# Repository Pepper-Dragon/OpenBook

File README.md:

# OpenBook
Proiect TSC - Diaconu Andrei 331CB

## Block Diagram

## Components

- **Microcontroller:** ESP32-C6 with integrated Wi-Fi 6 and Bluetooth 5 — responsible for core processing, communication, and power management.
- **Display:** 800×480 resolution e-Paper (e-Ink) display interfaced via SPI — ideal for low-power, high-visibility content rendering.
- **Sensors:** BME688 environmental sensor (temperature, humidity, pressure, air quality) connected through I2C.
- **Power Supply:** 2500mAh LiPo battery with USB-C charging and integrated fuel gauge for real-time battery monitoring.
- **Storage:** MicroSD card slot for storing e-books and other resources, communicating via SPI.
- **Real-Time Clock:** DS3231 RTC module with battery backup for accurate timekeeping even during power loss.
- **User Inputs:** 3 buttons (connected via GPIO) for navigation and control.
- **Expansion Options:** QWIIC/Stemma QT connector for easy integration of additional sensors or modules.

## Bill Of Materials

|                                   name                                   	|        value       	| description                                                           	| quantity 	|                                                                                                                                                     link                                                                                                                                                    	| datasheet                                                                                                                           	|
|:------------------------------------------------------------------------:	|:------------------:	|-----------------------------------------------------------------------	|:--------:	|:-----------------------------------------------------------------------------------------------------------------------------------------------------------------------------------------------------------------------------------------------------------------------------------------------------------:	|-------------------------------------------------------------------------------------------------------------------------------------	|
| LED1                                                                     	|          -         	| LED                                                                   	| 1        	| [link](https://www.niden.ro/led-uri-smd/4560-led-smd-0603-alb-rece.html)                                                                                                                                                                                                                                    	| [link](https://www.mouser.com/datasheet/2/423/LSM0603472V_(1)-1379786.pdf?srsltid=AfmBOoqdcB2pVIrWRImdZdFZcxn5SIjNLKeNM1u-ULY7G7UgiZHJYMAt)	|
| C18                                                                      	|      0.1uF/50V     	| CAPACITOR, European symbol                                            	| 1        	| [link](https://ro.mouser.com/ProductDetail/KEMET/C0402C104K4RAC7411?qs=GedzDrHbfJPMv36lRRfk4g%3D%3D)                                                                                                                                                                                                                	| [link](https://ro.mouser.com/datasheet/2/447/KEM_C1002_X7R_SMD-3316098.pdf)                                                                 	|
| R5                                                                       	|        0.47        	| RESISTOR, European symbol                                             	| 1        	| [link](https://ro.mouser.com/ProductDetail/ROHM-Semiconductor/SFR01MZPJ471?qs=sGAEpiMZZMtlubZbdhIBIONtIqra%2FA5YbUieG7R0owU%3D)                                                                                                                                                                                     	| [link](https://fscdn.rohm.com/en/products/databook/datasheet/passive/resistor/chip_resistor/sfr-e.pdf)                                      	|
| R1                                                                       	|        100K        	| RESISTOR, European symbol                                             	| 1        	| [link](https://ro.mouser.com/ProductDetail/Bourns/CR0402-FX-1003GLF?qs=URDPQ%2Fj0cz1ZruPSJQ7fsA%3D%3D&utm_id=6470900573&utm_source=google&utm_medium=cpc&utm_marketing_tactic=emeacorp&gad_source=1&gclid=CjwKCAjwzMi_BhACEiwAX4YZUExf8o5xv9o__WAln9moW8yaWJv0M179-dCfAxoyQP6_ulvhYGGM9xoCahIQAvD_BwE)              	| [link](https://ro.mouser.com/datasheet/2/54/cr-1858361.pdf)                                                                                 	|
| C1, C5, C21, C22, C23, C25, C26, C27                                     	|        100nF       	| CAPACITOR, European symbol                                            	| 8        	| [link](https://ro.mouser.com/ProductDetail/KEMET/C0402C104K4RAC7411?qs=GedzDrHbfJPMv36lRRfk4g%3D%3D)                                                                                                                                                                                                                	| [link](https://ro.mouser.com/datasheet/2/447/KEM_C1002_X7R_SMD-3316098.pdf)                                                                 	|
| C2                                                                       	|        100uF       	| POLARIZED CAPACITOR, European symbol                                  	| 1        	| [link](https://ro.mouser.com/ProductDetail/KEMET/T491B107M006AT?qs=U312oeP%2FpiHOgyk6KO2m0g%3D%3D)                                                                                                                                                                                                                  	| [link](https://ro.mouser.com/datasheet/2/447/KEM_T2005_T491-3316937.pdf)                                                                    	|
| R18                                                                      	|         10K        	| RESISTOR, European symbol                                             	| 1        	| [link](https://ro.mouser.com/ProductDetail/Vishay-Dale/CRCW040210K0FKEDC?qs=E3Y5ESvWgWPiNLcGzwCGPg%3D%3D)                                                                                                                                                                                                           	| [link](https://www.vishay.com/docs/28773/crcwce3.pdf)                                                                                       	|
| R6, R10, R11, R12, R13, R14, R15, R16, R19, R20, R21, R22, R23, R24, R25 	|         10k        	| RESISTOR, European symbol                                             	| 15       	| [link](https://ro.mouser.com/ProductDetail/Vishay-Dale/CRCW040210K0FKEDC?qs=E3Y5ESvWgWPiNLcGzwCGPg%3D%3D)                                                                                                                                                                                                           	| [link](https://www.vishay.com/docs/28773/crcwce3.pdf)                                                                                       	|
| C7                                                                       	|        10uF        	| CAPACITOR, European symbol                                            	| 1        	| [link](https://ro.mouser.com/ProductDetail/KEMET/C0402C106M7PAC7867?qs=kZJHmUDErizJnkDIcqVWRQ%3D%3D)                                                                                                                                                                                                                	| [link](https://ro.mouser.com/datasheet/2/447/KEM_C1006_X5R_SMD-3316465.pdf)                                                                 	|
| J1                                                                       	|          -         	| Micro SD Card Socket, Push-Push Type, Top   Mount, SMT, H=1.83mm, 10u 	| 1        	| [link](https://www.digikey.ro/en/products/detail/attend-technology/112A-TAAR-R03/17633923)                                                                                                                                                                                                                          	| [link](https://www.attend.com.tw/data/download/file/112A-TAAR-R03_Spec.pdf)                                                                 	|
| R17                                                                      	|         15         	| RESISTOR, European symbol                                             	| 1        	| [link](https://www.soselectronic.com/ro-ro/products/yageo/r0402-5-15-r-rc0402jr-0715rl-1-81614)                                                                                                                                                                                                                     	| [link](https://cdn.soselectronic.com/productdata/4b/af/65353ac1/r0402-1-1-5-k-rc0402fr-071k5l-1.pdf)                                        	|
| C24                                                                      	|         1uF        	| CAPACITOR, European symbol                                            	| 1        	| [link](https://ro.mouser.com/ProductDetail/KEMET/C0402C105Z9VACTU?qs=gt1LBUVyoHlQieoJt4iw1w%3D%3D)                                                                                                                                                                                                                  	| [link](https://ro.mouser.com/datasheet/2/447/KEM_C1005_Y5V_SMD-3316374.pdf)                                                                 	|
| C11, C12, C13, C14, C15, C16, C17, C19, C20                              	|       1uF/50V      	| CAPACITOR, European symbol                                            	| 9        	| [link](https://ro.mouser.com/ProductDetail/KEMET/C0402C105Z9VACTU?qs=gt1LBUVyoHlQieoJt4iw1w%3D%3D)                                                                                                                                                                                                                  	| [link](https://ro.mouser.com/datasheet/2/447/KEM_C1005_Y5V_SMD-3316374.pdf)                                                                 	|
| R7                                                                       	|         2.2        	| RESISTOR, European symbol                                             	| 1        	| [link](https://ro.mouser.com/ProductDetail/Panasonic/ERJ-PA2J2R2X?qs=sGAEpiMZZMtlubZbdhIBIKn8wLs5z3UnO%252BN6Zqj8Y2A%3D)                                                                                                                                                                                            	| [link](https://industrial.panasonic.com/cdbs/www-data/pdf/RDO0000/AOA0000C331.pdf)                                                          	|
| R8                                                                       	|         200        	| RESISTOR, European symbol                                             	| 1        	| [link](https://ro.mouser.com/ProductDetail/Vishay-Thin-Film/PNM0402E2000BSTS?qs=sGAEpiMZZMvdGkrng054t2cqbZCzJY7NtycrwNLdAiqcSryq%252B1Rhtw%3D%3D)                                                                                                                                                                   	| [link](https://www.vishay.com/docs/60057/pnm.pdf)                                                                                           	|
| Q1, Q3                                                                   	| 20V/4.2A/52mO/1.4W 	| P-channel MOSFETs                                                     	| 2        	| [link](https://www.digikey.ro/en/products/detail/vishay-siliconix/SI1308EDL-T1-GE3/4876435?utm_campaign=buynow&utm_medium=aggregator&utm_source=snapeda)                                                                                                                                                            	| [link](https://www.vishay.com/docs/63399/si1308edl.pdf)                                                                                     	|
| R9                                                                       	|         2k         	| RESISTOR, European symbol                                             	| 1        	| [link](https://ro.mouser.com/ProductDetail/Vishay-Dale/CRCW04022K00FKEE?qs=raETa%252B32nO8lGcRW9MjUBA%3D%3D)                                                                                                                                                                                                        	| [link](https://www.vishay.com/docs/20035/dcrcwe3.pdf)                                                                                       	|
| C6, C9, C10                                                              	|        4.7uF       	| CAPACITOR, European symbol                                            	| 3        	| [link](https://ro.mouser.com/ProductDetail/KEMET/C0402C475K8PACTU?qs=ulEaXIWI0c9ebKRT3r3htg%3D%3D)                                                                                                                                                                                                                  	| [link](https://ro.mouser.com/datasheet/2/447/KEM_C1006_X5R_SMD-3316465.pdf)                                                                 	|
| C3, C4                                                                   	|        4.7uF       	| CAPACITOR, European symbol                                            	| 2        	| [link](https://ro.mouser.com/ProductDetail/KEMET/C0402C475K8PACTU?qs=ulEaXIWI0c9ebKRT3r3htg%3D%3D)                                                                                                                                                                                                                  	| [link](https://ro.mouser.com/datasheet/2/447/KEM_C1006_X5R_SMD-3316465.pdf)                                                                 	|
| C8                                                                       	|      4.7uF/25V     	| CAPACITOR, European symbol                                            	| 1        	| [link](https://ro.mouser.com/ProductDetail/KEMET/C0402C475K8PACTU?qs=ulEaXIWI0c9ebKRT3r3htg%3D%3D)                                                                                                                                                                                                                  	| [link](https://ro.mouser.com/ProductDetail/KEMET/C0402C475K8PACTU?qs=ulEaXIWI0c9ebKRT3r3htg%3D%3D)                                          	|
| D3                                                                       	|      4.7uF/25V     	| ON SEMICONDUCTOR - MBR0530 - DIODE,   SCHOTTKY, 0.5A, 30V, SOD-123    	| 1        	| [link](https://www.snapeda.com/parts/MBR0530/Onsemi/view-part/?ref=eda)                                                                                                                                                                                                                                             	| [link](https://www.snapeda.com/parts/MBR0530/ON%20Semiconductor/datasheet/)                                                                 	|
| R3, R4                                                                   	|         5k1        	| RESISTOR, European symbol                                             	| 2        	| [link](https://www.gme.cz/v/1484336/yageo-r0402-5k1-006w-1-smd-rezistor?srsltid=AfmBOooJFe0JuMtJCHsiAAMzt535X2PaRQWliIdlncts6E1iAX--2xYh)                                                                                                                                                                           	| [link](https://img.gme.cz/files/eshop_data/eshop_data/7/984-017/dsh.984-017.1.pdf)                                                          	|
| L1                                                                       	|        68uH        	| coil                                                                  	| 1        	| [link](https://ro.mouser.com/ProductDetail/Wurth-Elektronik/744043680?qs=PGXP4M47uW6VkZq%252BkzjrHA%3D%3D)                                                                                                                                                                                                          	| [link](https://www.we-online.com/components/products/datasheet/744043680.pdf)                                                               	|
| IC2                                                                      	|          -         	| Voltage Detector with Adjustable Delay                                	| 1        	| [link](https://ro.mouser.com/ProductDetail/ROHM-Semiconductor/BD5229G-TR?qs=4kLU8WoGk0vvnhrrYwdszw%3D%3D)                                                                                                                                                                                                           	| [link](https://fscdn.rohm.com/en/products/databook/datasheet/ic/power/voltage_detector/bd52xxg-e.pdf)                                       	|
| BOOT_BUTTON, CHANGE_BUTTON, RESET_BUTTON                                 	|          -         	| Button                                                                	| 3        	| [link](https://ro.mouser.com/ProductDetail/CK/PTS841-GK-SMTR-LFS?qs=d0WKAl%252BL4KbAtAqJT9yhkg%3D%3D)                                                                                                                                                                                                               	| [link](https://www.ckswitches.com/media/2805/pts841.pdf)                                                                                    	|
| C28                                                                      	|          -         	| Cap 0.011F 3.3V 1210 Flat                                             	| 1        	| [link](https://www.snapeda.com/parts/CPH3225A/Seiko+Instruments/view-part/?ref=eda)                                                                                                                                                                                                                                 	| [link](https://www.snapeda.com/parts/CPH3225A/Seiko%20Instruments/datasheet/)                                                               	|
| U5                                                                       	|          -         	| Real Time Clock Serial 16-Pin SOIC W   T/R                            	| 1        	| [link](https://www.snapeda.com/parts/DS3231SN%23/Analog+Devices/view-part/?ref=eda)                                                                                                                                                                                                                                 	| [link](https://www.snapeda.com/parts/DS3231SN%23/Analog%20Devices/datasheet/)                                                               	|
| U2                                                                       	|          -         	| ESP32                                                                 	| 1        	| [link](https://www.snapeda.com/parts/ESP32-C6-WROOM-1-N8/Espressif+Systems/view-part/?ref=eda)                                                                                                                                                                                                                      	| [link](https://www.snapeda.com/parts/ESP32-C6-WROOM-1-N8/Espressif%20Systems/datasheet/)                                                    	|
| R2                                                                       	|          -         	| VARISTOR                                                              	| 1        	| [link](https://www.digikey.ro/en/products/detail/epcos-tdk-electronics/B72580T0110K062/15903564)                                                                                                                                                                                                                    	| [link](https://www.tdk-electronics.tdk.com/inf/75/db/CTVS_14/Standard_series.pdf)                                                           	|
| D1, D6                                                                   	|          -         	| Schottky Barrier Rectifier Diode                                      	| 2        	| [link](https://eu.mouser.com/ProductDetail/KYOCERA-AVX/SD0805S020S1R0?qs=jCA%252BPfw4LHbpkAoSnwrdjw%3D%3D&srsltid=AfmBOoos7vAXHpuNsFyDZDH2ms56jfFYgACPLwGeQRLBDVu-QQCPVRyy)                                                                                                                                         	| [link](https://ro.mouser.com/datasheet/2/40/schottky-3165252.pdf)                                                                           	|
| U3                                                                       	|          -         	| Integrated Environmental Unit                                         	| 1        	| [link](https://ro.mouser.com/ProductDetail/Bosch-Sensortec/BME680?qs=v271MhAjFHjo0yA%2FC4OnDQ%3D%3D)                                                                                                                                                                                                                	| [link](https://ro.mouser.com/datasheet/2/783/BST_BME680_DS001-1509608.pdf)                                                                  	|
| U1                                                                       	|          -         	| MCP73831T Li-Ion, Li-Pol Controller                                   	| 1        	| [link](https://eu.mouser.com/ProductDetail/Microchip-Technology/MCP73831T-2ACI-OT?qs=yUQqVecv4qvbBQBGbHx0Mw%3D%3D&utm_id=20109199409&utm_source=google&utm_medium=cpc&utm_marketing_tactic=emeacorp&gad_source=1&gclid=CjwKCAjwzMi_BhACEiwAX4YZUFXFfoOvOVw-rJ3AqbhBnSMrJwio_-4FjBZgwNJVbUQHlwwnAKDqhBoCYr4QAvD_BwE) 	| [link](https://ro.mouser.com/datasheet/2/268/MCP73831_Family_Data_Sheet_DS20001984H-3441711.pdf)                                            	|
| J3                                                                       	|          -         	|  (0.50mm) Surface Mount, Right Angle                                  	| 1        	| [link](https://ro.mouser.com/ProductDetail/Hirose-Connector/FH34SRJ-24S-0.5SH99?qs=vcbW%252B4%252BSTIpKBl5ap9J8Fw%3D%3D&_gl=1*l9suft*_ga*MTI5Mzc0MzA3OS4xNzQzODQ5MDQz*_ga_15W4STQT4T*MTc0Mzk1NTYyNy40LjAuMTc0Mzk1NTYyNy42MC4wLjA.)                                                                                  	| [link](https://ro.mouser.com/datasheet/2/185/FH34SRJ_24S_0_5SH_99__CL0580_1255_6_99_2DDrawing_0-1615044.pdf)                                	|
| U4                                                                       	|          -         	| 3µA 1-Cell/2-Cell Fuel Gauge with ModelGauge                          	| 1        	| [link](https://www.snapeda.com/parts/MAX17048G+T10/Analog+Devices/view-part/?ref=eda)                                                                                                                                                                                                                               	| [link](https://www.snapeda.com/parts/MAX17048G+T10/Analog%20Devices/datasheet/)                                                             	|
| D4, D5                                                                   	|          -         	| DIODE,   SCHOTTKY, 0.5A, 30V, SOD-123                                 	| 2        	| [link](https://www.snapeda.com/parts/MBR0530/Onsemi/view-part/?ref=eda)                                                                                                                                                                                                                                             	| [link](https://www.snapeda.com/parts/MBR0530/ON%20Semiconductor/datasheet/)                                                                 	|
| D7, D8, D9, D10, D11, D12                                                	|          -         	| Ipp Tvs Diode                                                         	| 6        	| [link](https://www.snapeda.com/parts/PGB1010603MR/Littelfuse/view-part/?ref=eda)                                                                                                                                                                                                                                    	| [link](https://www.snapeda.com/parts/PGB1010603MR/Littelfuse%20Inc./datasheet/)                                                             	|
| J4                                                                       	|          -         	| SparkFun I2C Standard Qwiic Connector                                 	| 1        	| [link](https://www.sparkfun.com/qwiic-jst-connector-smd-4-pin-horizontal.html)                                                                                                                                                                                                                                      	| [link](https://cdn.sparkfun.com/assets/parts/1/2/2/8/9/Qwiic_Connector_Datasheet.pdf)                                                       	|
| J2                                                                       	|          -         	| CONN USB 2.0 TYPE-C R/A SMT                                           	| 1        	| [link](https://ro.mouser.com/ProductDetail/GCT/USB4110-GF-A?qs=KUoIvG%2F9IlYiZvIXQjyJeA%3D%3D)                                                                                                                                                                                                                      	| [link](https://ro.mouser.com/datasheet/2/837/GCT_USB4110_Product_Drawing___20k_cycles-3455479.pdf)                                          	|
| Q2                                                                       	|          -         	| MOSFET N-Ch 30V 1.5A                                                  	| 1        	| [link](https://www.snapeda.com/parts/SI1308EDL-T1-GE3/Vishay+Siliconix/view-part/?ref=eda)                                                                                                                                                                                                                          	| [link](https://www.snapeda.com/parts/SI1308EDL-T1-GE3/Vishay%20Siliconix/datasheet/)                                                        	|
| D2                                                                       	|          -         	| Low Cap. ESD Protection Auto SOT-23-6                                 	| 1        	| [link](https://www.snapeda.com/parts/USBLC6-2SC6Y/STMicroelectronics/view-part/?ref=eda)                                                                                                                                                                                                                            	| [link](https://www.snapeda.com/parts/USBLC6-2SC6Y/STMicroelectronics/datasheet/)                                                            	|
| U6                                                                       	|          -         	| FLASH - NOR Memory IC 512Mb                                           	| 1        	| [link](https://www.snapeda.com/parts/W25Q512JVEIQ/Winbond+Electronics/view-part/?ref=eda)                                                                                                                                                                                                                           	| [link](https://www.snapeda.com/parts/W25Q512JVEIQ/Winbond%20Electronics/datasheet/)                                                         	|
| IC1                                                                      	|          -         	| LDO Voltage Regulator                                                 	| 1        	| [link](https://ro.mouser.com/ProductDetail/Torex-Semiconductor/XC6220A331MR-G?qs=AsjdqWjXhJ8ZSWznL1J0gg%3D%3D&utm_id=6470900573&utm_source=google&utm_medium=cpc&utm_marketing_tactic=emeacorp&gad_source=1&gclid=CjwKCAjwzMi_BhACEiwAX4YZUHiB3kDs66vv29tGnRc8y1huoaOvdBlKkwXVy8QKs7T5wBQH4NGZUxoCU5wQAvD_BwE)      	| [link](https://ro.mouser.com/datasheet/2/760/xc6220-3371556.pdf)                                                                            	|

## ESP32-C6 Pins

| Connection      | Pin            | Description                                                               |
|-----------------|----------------|---------------------------------------------------------------------------|
| **RESET**       | EN             | Reset button for initiating a reset sequence                              |
| **INT_RTC**     | IO0            | Interrupt signal for the RTC                                              |
| **32KHZ**       | IO1            | Input for 32kHz clock signal                                              |
| **MISO**        | IO2            | Master In Slave Out for communication between the microcontroller, Flash, SD Card, and display |
| **EPD_BUSY**    | IO3            | Signal indicating if the display is busy                                  |
| **SS_SD**       | IO4            | Chip select for the SD card                                               |
| **EPD_DC**      | IO5            | Display data/command control pin                                          |
| **SCK**         | IO6            | SPI clock for synchronizing data transfers                                |
| **MOSI**        | IO7            | Master Out Slave In for data transmission between the microcontroller, Flash, SD card, and display |
| **3V3**         | IO8            | 3.3V power supply                                                          |
| **IO/BOOT**     | IO9            | Boot button to trigger boot process                                       |
| **EPD_CS**      | IO10           | Chip select for the display                                               |
| **FLASH_CS**    | IO11           | Chip select for the Flash memory                                          |
| **USB_D-**      | IO12           | USB data negative for communication                                       |
| **USB_D+**      | IO13           | USB data positive for communication                                       |
| **IO/CHANGE**   | IO15           | Button to trigger a change action                                         |
| **TX (UART)**   | TXD0 / GPIO16  | Serial transmitter for UART communication                                 |
| **RX (UART)**   | RXD0 / GPIO17  | Serial receiver for UART communication                                    |
| **RTC_RST**     | IO18           | External reset for the RTC module                                         |
| **I2C_PW**      | IO19           | Power control signal for I2C devices                                      |
| **EPD_3V3_C**   | IO20           | 3.3V power supply for the display                                         |
| **SDA (I2C)**   | IO21           | Data line for I2C communication (e.g., RTC, BME688, Battery Gauge)       |
| **SCL (I2C)**   | IO22           | Clock line for I2C synchronization                                        |
| **EPD_RST**     | IO23           | Reset signal for the display                                              |
| **3V3**         | 3V3            | 3.3V power line                                                           |
| **GND**         | GND            | Ground connection                                                         |

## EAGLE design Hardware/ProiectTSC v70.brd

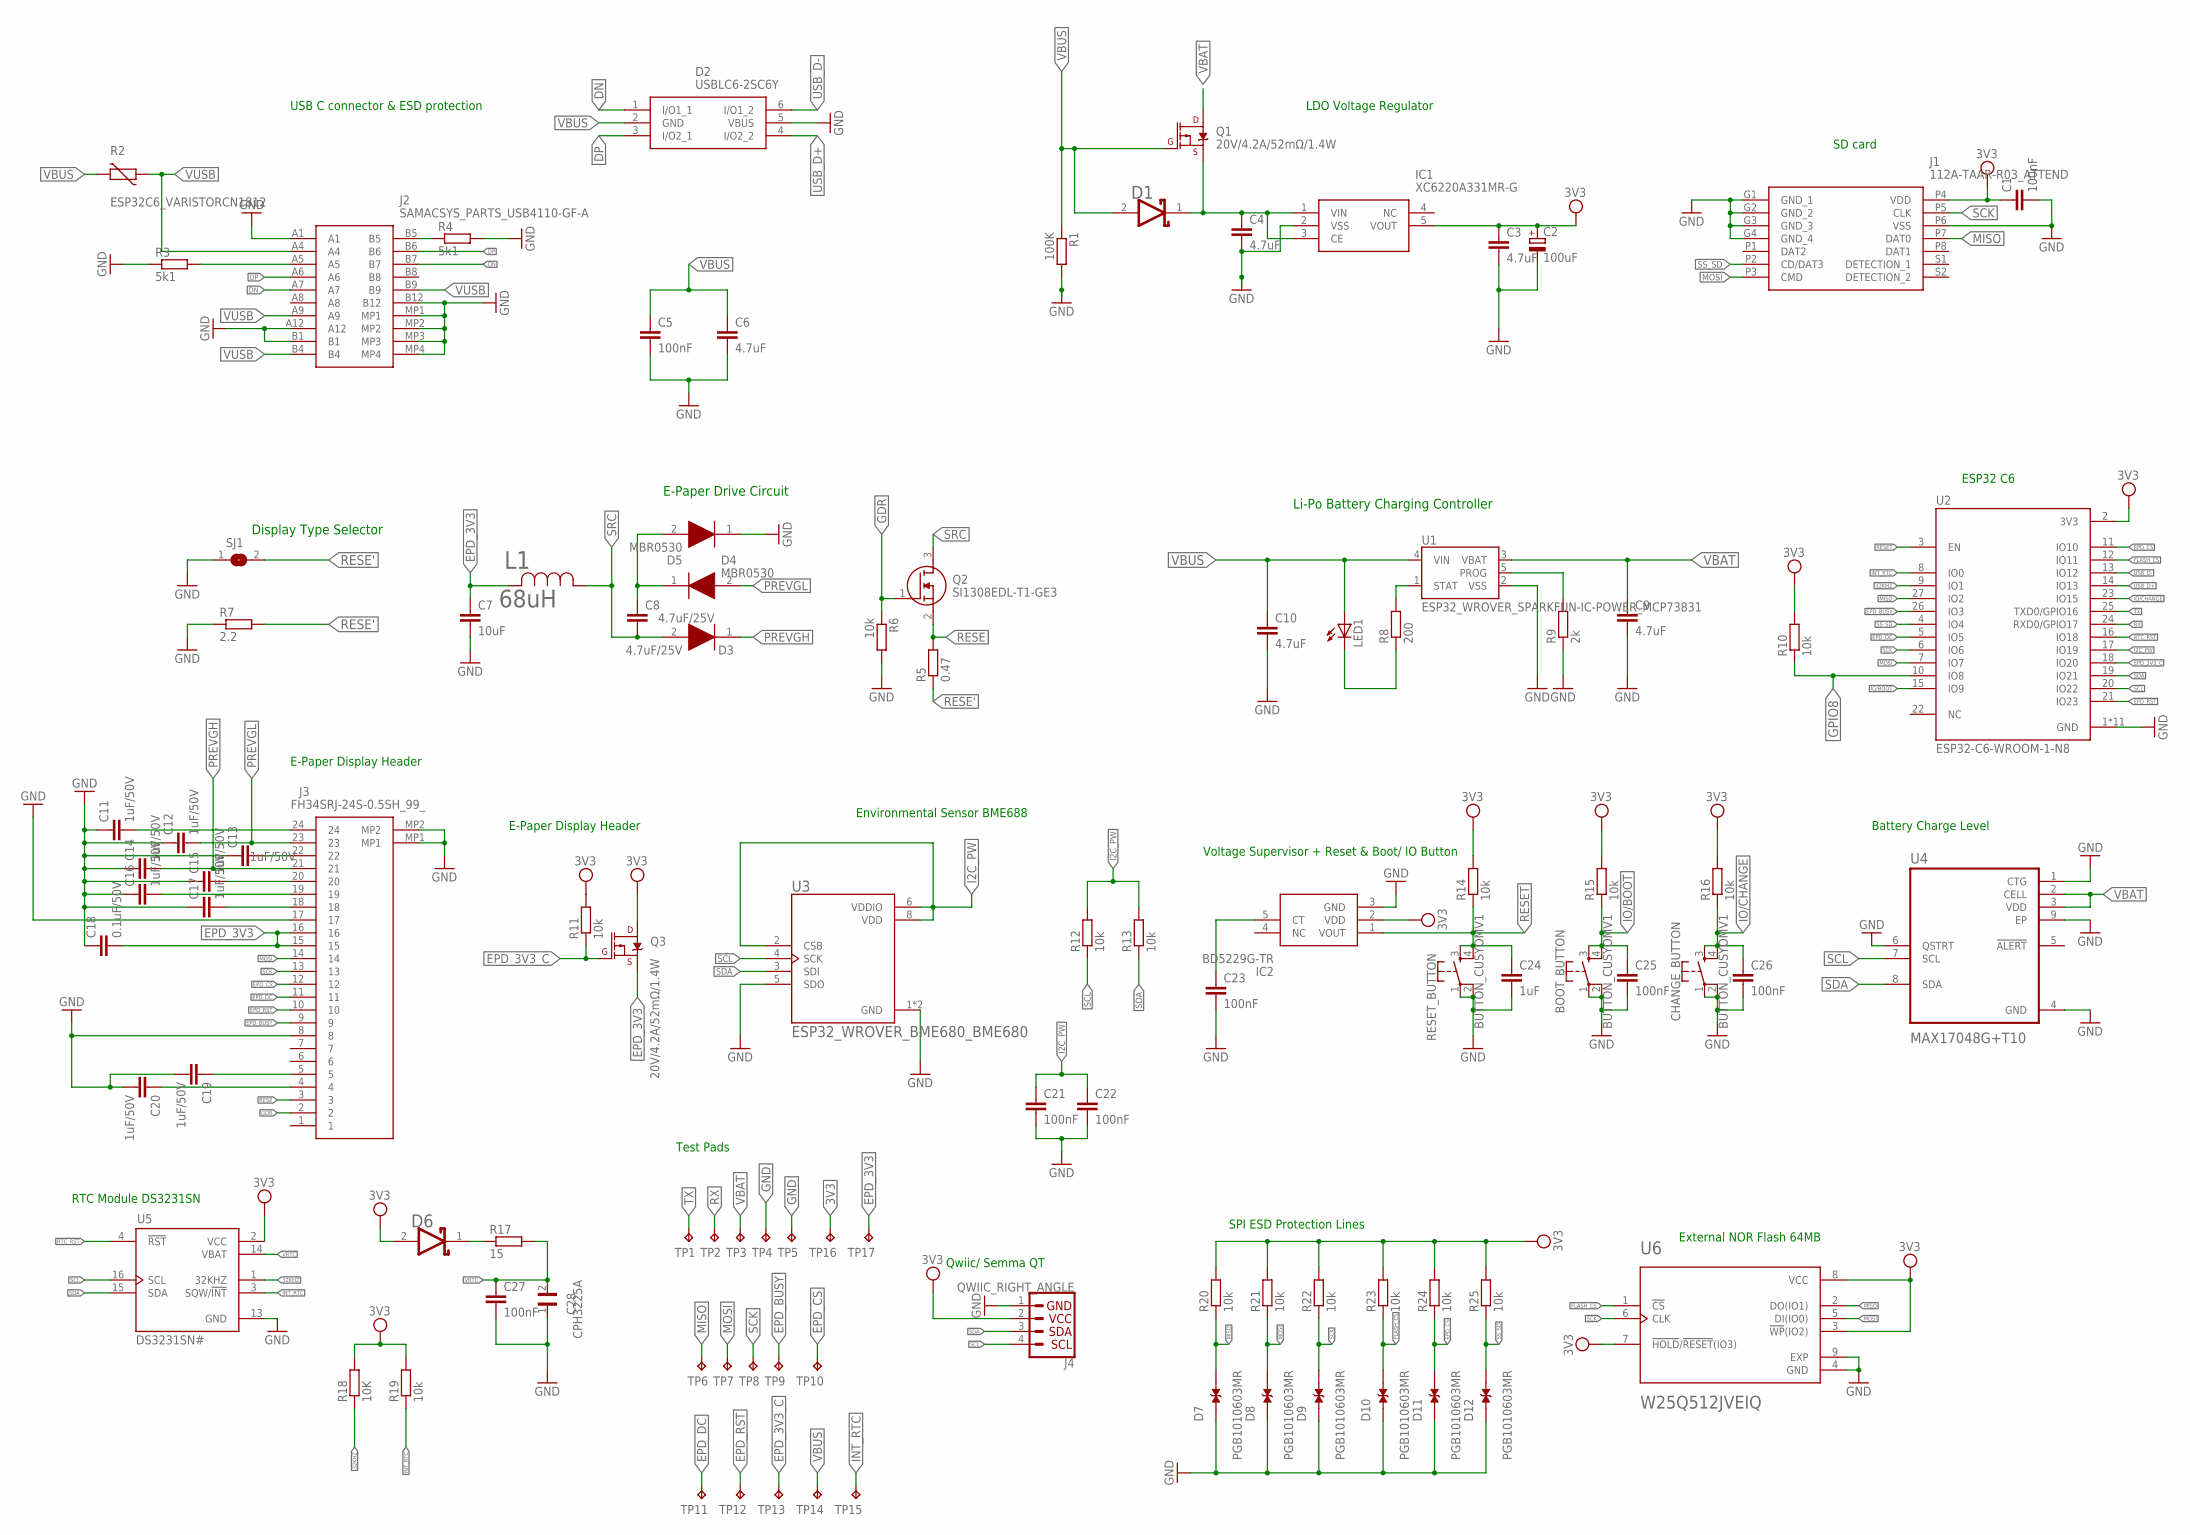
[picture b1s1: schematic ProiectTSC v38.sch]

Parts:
BOOT_BUTTON: BUTTON_CUSYOMV1; MYBUTTON
C1, C5, C21, C22, C23, C25, C26, C27: 100nF; EAGLE-LTSPICE_C0402
C2: 100uF; RCL_CT3528
C3, C4: 4.7uF; ESP32_WROVER_EAGLE-LTSPICE_C0402
C6, C9, C10: 4.7uF; EAGLE-LTSPICE_C0402
C7: 10uF; EAGLE-LTSPICE_C0402
C8: 4.7uF/25V; EAGLE-LTSPICE_C0402
C11, C12, C13, C14, C15, C16, C17, C19, C20: 1uF/50V; EAGLE-LTSPICE_C0402
C18: 0.1uF/50V; EAGLE-LTSPICE_C0402
C24: 1uF; EAGLE-LTSPICE_C0402
C28: CPH3225A; CAPCP3225X100N
CHANGE_BUTTON: BUTTON_CUSYOMV1; MYBUTTON
D1, D6: ESP32_WROVER_AVX---SD0805S020S1R0_AVX_SD0805S020S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; ESP32_WROVER_AVX---SD0805S020S1R0_AVX_SD0805S020S1R0_0
D2: USBLC6-2SC6Y; SOT95P280X145-6N
D3: 4.7uF/25V; SOD3716X135N
D4, D5: MBR0530; SOD3716X135N
D7, D8, D9, D10, D11, D12: PGB1010603MR; DIOC1608X36N
IC1: XC6220A331MR-G; SOT95P280X120-5N
IC2: BD5229G-TR; SOT95P280X125-5N
J1: 112A-TAAR-R03_ATTEND; 112ATAARR03ATTEND
J2: SAMACSYS_PARTS_USB4110-GF-A; SAMACSYS_PARTS_USB4110GFA
J3: FH34SRJ-24S-0.5SH_99_; FH34SRJ24S05SH99
J4: QWIIC_RIGHT_ANGLE; JST04_1MM_RA
L1: 68uH; IND_4828-WE-TPC_WRE
LED1: ADAFRUIT_LEDCHIP-LED0603; ADAFRUIT_CHIP-LED0603
Q1, Q3: 20V/4.2A/52mΩ/1.4W; ESP32_WROVER_SPARKFUN-DISCRETESEMI_SOT23-3
Q2: SI1308EDL-T1-GE3; SOT65P210X110-3N
R1: 100K; ESP32_WROVER_EAGLE-LTSPICE_R0402
R2: ESP32C6_VARISTORCN1812; ESP32C6_VARISTOR_CT/CN1812
R3, R4: 5k1; ESP32_WROVER_EAGLE-LTSPICE_R0402
R5: 0.47; ESP32_WROVER_EAGLE-LTSPICE_R0402
R6, R10, R11, R12, R13, R14, R15, R16, R19, R20, R21, R22, R23, R24, R25: 10k; ESP32_WROVER_EAGLE-LTSPICE_R0402
R7: 2.2; ESP32_WROVER_EAGLE-LTSPICE_R0402
R8: 200; ESP32_WROVER_EAGLE-LTSPICE_R0402
R9: 2k; ESP32_WROVER_EAGLE-LTSPICE_R0402
R17: 15; ESP32_WROVER_EAGLE-LTSPICE_R0402
R18: 10K; ESP32_WROVER_EAGLE-LTSPICE_R0402
RESET_BUTTON: BUTTON_CUSYOMV1; MYBUTTON
SJ1: SJ
TP1, TP2, TP3, TP4, TP5, TP6, TP7, TP8, TP9, TP10, TP11, TP12, TP13, TP14, TP15, TP16, TP17: TPTP20R; TP20R
U1: ESP32_WROVER_SPARKFUN-IC-POWER_MCP73831; ESP32_WROVER_SPARKFUN-IC-POWER_SOT23-5
U2: ESP32-C6-WROOM-1-N8; XCVR_ESP32-C6-WROOM-1-N8
U3: ESP32_WROVER_BME680_BME680; ESP32_WROVER_BME680_PSON80P300X300X100-8N
U4: MAX17048G+T10; SON50P200X200X80-9N
U5: DS3231SN#; SOIC127P1032X265-16N
U6: W25Q512JVEIQ; SON127P600X800X80-9N

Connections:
3V3: C1.1, C2.+, C3.1, D6.2 (ANODE), IC1.5 (VOUT), IC2.2 (VDD), J1.P4 (VDD), J4.2, Q3.3 (D), R10.2, R11.2, R14.2, R15.2, R16.2, R18.2, R19.2, R20.2, R21.2, R22.2, R23.2, R24.2, R25.2, TP16.TP, U2.2 (3V3), U5.2 (VCC), U6.3 (!WP!(IO2)), U6.7 (!HOLD!/!RESET!(IO3)), U6.8 (VCC)
32KHZ: R18.1, U2.9 (IO1), U5.1 (32KHZ)
DN: D2.1 (I/O1_1), J2.A7, J2.B7
DP: D2.3 (I/O2_1), J2.A6, J2.B6
EPD_3V3: C7.1, C18.2, J3.15, J3.16, L1.2, Q3.2 (S), TP17.TP
EPD_3V3_C: Q3.1 (G), R11.1, TP13.TP, U2.18 (IO20)
EPD_BUSY: J3.9, TP9.TP, U2.26 (IO3)
EPD_CS: D11.2, J3.12, R24.1, TP10.TP, U2.11 (IO10)
EPD_DC: J3.11, TP11.TP, U2.5 (IO5)
EPD_RST: J3.10, TP12.TP, U2.21 (IO23)
FLASH_CS: D10.2, R23.1, U2.12 (IO11), U6.1 (!CS)
GDR: J3.2, Q2.1 (G), R6.1
GND: BOOT_BUTTON.1, BOOT_BUTTON.2, C1.2, C2.-, C3.2, C4.2, C5.2, C6.2, C7.2, C9.2, C10.2, C11.1, C12.1, C13.1, C14.1, C15.1, C16.1, C17.1, C18.1, C19.2, C20.2, C21.2, C22.2, C23.2, C24.2, C25.2, C26.2, C27.2, C28.1, CHANGE_BUTTON.1, CHANGE_BUTTON.2, D2.5 (VBUS), D5.1 (K), D7.1, D8.1, D9.1, D10.1, D11.1, D12.1, IC1.2 (VSS), IC2.3 (GND), J1.G1 (GND_1), J1.G2 (GND_2), J1.G3 (GND_3), J1.G4 (GND_4), J1.P6 (VSS), J2.A1, J2.A12, J2.B1, J2.B12, J2.MP1, J2.MP2, J2.MP3, J2.MP4, J3.8, J3.17, J3.MP1, J3.MP2, J4.1, R1.2, R3.1, R4.2, R6.2, R7.1, R9.1, RESET_BUTTON.1, RESET_BUTTON.2, SJ1.1, TP4.TP, TP5.TP, U1.2 (VSS), U2.1 (GND), U2.28 (GND), U2.29_1 (GND), U2.29_2 (GND), U2.29_3 (GND), U2.29_4 (GND), U2.29_5 (GND), U2.29_6 (GND), U2.29_7 (GND), U2.29_8 (GND), U2.29_9 (GND), U3.1 (GND), U3.5 (SDO), U3.7 (GND), U4.1 (CTG), U4.4 (GND), U4.6 (QSTRT), U4.9 (EP), U5.13 (GND), U6.4 (GND), U6.9 (EXP)
GPIO8: R10.1, U2.10 (IO8)
I2C_PW: C21.1, C22.1, R12.2, R13.2, U2.17 (IO19), U3.2 (CSB), U3.6 (VDDIO), U3.8 (VDD)
INT_RTC: R19.1, TP15.TP, U2.8 (IO0), U5.3 (SQW/!INT)
IO/BOOT: BOOT_BUTTON.3, BOOT_BUTTON.4, C25.1, R15.1, U2.15 (IO9)
IO/CHANGE: C26.1, CHANGE_BUTTON.3, CHANGE_BUTTON.4, R16.1, U2.23 (IO15)
MISO: D7.2, J1.P7 (DAT0), R20.1, TP6.TP, U2.27 (IO2), U6.2 (DO(IO1))
MOSI: D8.2, J1.P3 (CMD), J3.14, R21.1, TP7.TP, U2.7 (IO7), U6.5 (DI(IO0))
unnamed: J2.B5, R4.1
unnamed: C11.2, J3.24
unnamed: C8.1, D4.1 (K), D5.2 (A)
unnamed: J2.A5, R3.2
unnamed: C19.1, J3.5
unnamed: C4.1, D1.1 (CATHODE), IC1.1 (VIN), IC1.3 (CE), Q1.2 (S)
unnamed: R9.2, U1.5 (PROG)
unnamed: C23.1, IC2.5 (CT)
unnamed: C20.1, J3.4
unnamed: C13.2, J3.22
unnamed: R8.2, U1.1 (STAT)
unnamed: LED1.C, R8.1
unnamed: D6.1 (CATHODE), R17.1
unnamed: C15.2, J3.20
unnamed: C16.2, J3.19
unnamed: C17.2, J3.18
PREVGH: C14.2, D3.1 (K), J3.21
PREVGL: C12.2, D4.2 (A), J3.23
RESE: J3.3, Q2.2 (S), R5.2
RESE': R5.1, R7.2, SJ1.2
RESET: C24.1, IC2.1 (VOUT), R14.1, RESET_BUTTON.3, RESET_BUTTON.4, U2.3 (EN)
RTC_RST: U2.16 (IO18), U5.4 (!RST)
RX: TP2.TP, U2.24 (RXD0/GPIO17)
SCK: D9.2, J1.P5 (CLK), J3.13, R22.1, TP8.TP, U2.6 (IO6), U6.6 (CLK)
SCL: J4.4, R12.1, U2.20 (IO22), U3.4 (SCK), U4.7 (SCL), U5.16 (SCL)
SDA: J4.3, R13.1, U2.19 (IO21), U3.3 (SDI), U4.8 (SDA), U5.15 (SDA)
SRC: C8.2, D3.2 (A), L1.1, Q2.3 (D)
SS_SD: D12.2, J1.P2 (CD/DAT3), R25.1, U2.4 (IO4)
TX: TP1.TP, U2.25 (TXD0/GPIO16)
USB_D+: D2.4 (I/O2_2), U2.14 (IO13)
USB_D-: D2.6 (I/O1_2), U2.13 (IO12)
VBAT: C9.1, Q1.3 (D), TP3.TP, U1.3 (VBAT), U4.2 (CELL), U4.3 (VDD)
VBUS: C5.1, C6.1, C10.1, D1.2 (ANODE), D2.2 (GND), LED1.A, Q1.1 (G), R1.1, R2.2, TP14.TP, U1.4 (VIN)
VRTC: C27.1, C28.2, R17.2, U5.14 (VBAT)
VUSB: J2.A4, J2.A9, J2.B4, J2.B9, R2.1

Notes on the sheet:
SD card
LDO Voltage Regulator
USB C connector & ESD protection
E-Paper Drive Circuit
Display Type Selector
Li-Po Battery Charging Controller
ESP32 C6
E-Paper Display Header
Environmental Sensor BME688
Voltage Supervisor + Reset & Boot/ IO Button
Battery Charge Level
RTC Module DS3231SN
Test Pads
Qwiic/ Semma QT
SPI ESD Protection Lines
External NOR Flash 64MB

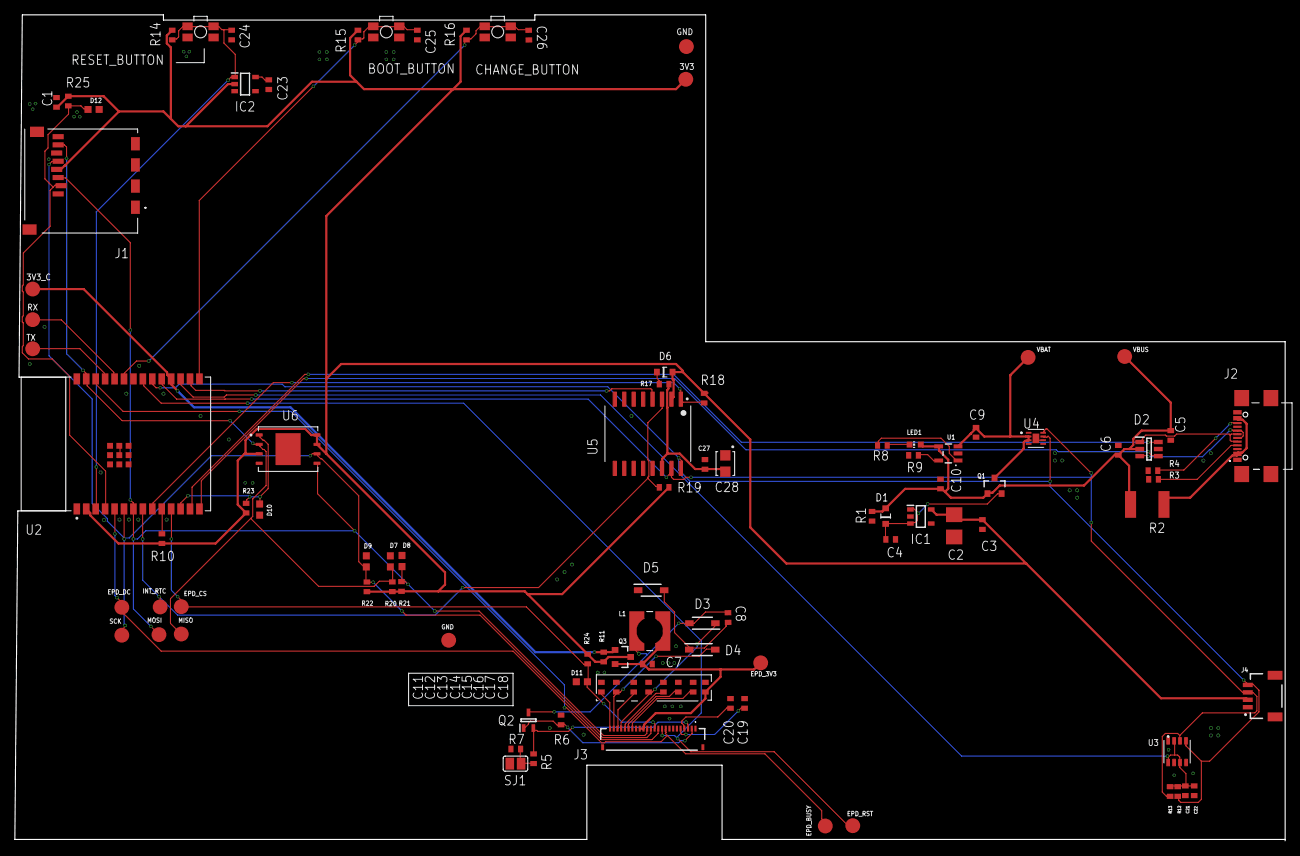
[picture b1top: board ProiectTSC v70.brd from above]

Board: 2 copper layers, 171.0 x 111.0 mm, 103 parts (0 on the bottom side), 55 nets.

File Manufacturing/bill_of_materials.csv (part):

Qty,Value,Device,Package,Parts,Description,ARROW_PART_NUMBER,ARROW_PRICE-STOCK,AVAILABILITY,CENTROID_NOT_SPECIFIED,CHECK_PRICES,COPYRIGHT,DATASHEET,DESCRIPTION,DIGIKEY_DESCRIPTION,DIGIKEY_PART_NUMBER,HEIGHT,LEAD_FREE,MANUFACTURER_NAME,MANUFACTURER_PART_NUMBER,MF,MFR_NAME,MOUSER_PART_NUMBER,MOUSER_PRICE-STOCK,MOUSER_TESTING_PART_NUMBER,MOUSER_TESTING_PRICE-STOCK,MP,MPN,PACKAGE,POPULARITY,PREFIX,PRICE,PROD_ID,PURCHASE-URL,ROHS,SNAPEDA_LINK,SPICEMODEL,SPICEPREFIX,TEMPERATURE_RANGE_HIGH,TEMPERATURE_RANGE_LOW,TP_SIGNAL_NAME,VALUE
1,,ADAFRUIT_LEDCHIP-LED0603,ADAFRUIT_CHIP-LED0603,LED1,LED,,,,,,,,,,,,,,,,,,,,,,,,,,,,,,,,,,,,
1,,SJ,SJ,SJ1,"SMD solder JUMPER",,,,,,,,,,,,,,,,,,,,,,,,3,,,,,,,,,,,,
1,0.1uF/50V,EAGLE-LTSPICE_CC0402,EAGLE-LTSPICE_C0402,C18,"CAPACITOR, European symbol",,,,,,,,,,,,,,,,,,,,,,,,,,,,,,,NONE,C,,,,
1,0.47,ESP32_WROVER_EAGLE-LTSPICE_RR0402,ESP32_WROVER_EAGLE-LTSPICE_R0402,R5,"RESISTOR, European symbol",,,,,,,,,,,,,,,,,,,,,,,,,,,,,,,NONE,R,,,,
1,100K,ESP32_WROVER_EAGLE-LTSPICE_RR0402,ESP32_WROVER_EAGLE-LTSPICE_R0402,R1,"RESISTOR, European symbol",,,,,,,,,,,,,,,,,,,,,,,,,,,,,,,NONE,R,,,,
8,100nF,EAGLE-LTSPICE_CC0402,EAGLE-LTSPICE_C0402,"C1, C5, C21, C22, C23, C25, C26, C27","CAPACITOR, European symbol",,,,,,,,,,,,,,,,,,,,,,,,,,,,,,,NONE,C,,,,
1,100uF,RCL_CPOL-EUCT3528,RCL_CT3528,C2,"POLARIZED CAPACITOR, European symbol",,,,,,,,,,,,,,,,,,,,,,,,0,,,,,,,,C,,,,
1,10K,ESP32_WROVER_EAGLE-LTSPICE_RR0402,ESP32_WROVER_EAGLE-LTSPICE_R0402,R18,"RESISTOR, European symbol",,,,,,,,,,,,,,,,,,,,,,,,,,,,,,,NONE,R,,,,
15,10k,ESP32_WROVER_EAGLE-LTSPICE_RR0402,ESP32_WROVER_EAGLE-LTSPICE_R0402,"R6, R10, R11, R12, R13, R14, R15, R16, R19, R20, R21, R22, R23, R24, R25","RESISTOR, European symbol",,,,,,,,,,,,,,,,,,,,,,,,,,,,,,,NONE,R,,,,
1,10uF,EAGLE-LTSPICE_CC0402,EAGLE-LTSPICE_C0402,C7,"CAPACITOR, European symbol",,,,,,,,,,,,,,,,,,,,,,,,,,,,,,,NONE,C,,,,
1,112A-TAAR-R03_ATTEND,112A-TAAR-R03_ATTEND,112ATAARR03ATTEND,J1,"Micro SD Card Socket, Push-Push Type, Top Mount, SMT, H=1.83mm, 10u",,,,,,,,"Micro SD Card Socket"," Push-Push Type"," Top Mount"," SMT"," H=1.83mm"," 10u",,,1.9mm,,ATTEND,"112A-TAAR-R03 ATTEND",,,,,,,,,,,,,,,,,
1,15,ESP32_WROVER_EAGLE-LTSPICE_RR0402,ESP32_WROVER_EAGLE-LTSPICE_R0402,R17,"RESISTOR, European symbol",,,,,,,,,,,,,,,,,,,,,,,,,,,,,,,NONE,R,,,,
1,1uF,EAGLE-LTSPICE_CC0402,EAGLE-LTSPICE_C0402,C24,"CAPACITOR, European symbol",,,,,,,,,,,,,,,,,,,,,,,,,,,,,,,NONE,C,,,,
9,1uF/50V,EAGLE-LTSPICE_CC0402,EAGLE-LTSPICE_C0402,"C11, C12, C13, C14, C15, C16, C17, C19, C20","CAPACITOR, European symbol",,,,,,,,,,,,,,,,,,,,,,,,,,,,,,,NONE,C,,,,
1,2.2,ESP32_WROVER_EAGLE-LTSPICE_RR0402,ESP32_WROVER_EAGLE-LTSPICE_R0402,R7,"RESISTOR, European symbol",,,,,,,,,,,,,,,,,,,,,,,,,,,,,,,NONE,R,,,,
1,200,ESP32_WROVER_EAGLE-LTSPICE_RR0402,ESP32_WROVER_EAGLE-LTSPICE_R0402,R8,"RESISTOR, European symbol",,,,,,,,,,,,,,,,,,,,,,,,,,,,,,,NONE,R,,,,
2,20V/4.2A/52mO/1.4W,ESP32_WROVER_SPARKFUN-DISCRETESEMI_MOSFET_PCH-DMG2305UX-7,ESP32_WROVER_SPARKFUN-DISCRETESEMI_SOT23-3,"Q1, Q3","P-channel MOSFETs",,,,,,,,,,,,,,,,,,,,,,,,,,,TRAN-14388,,,,,,,,,20V/4.2A/52mO/1.4W
1,2k,ESP32_WROVER_EAGLE-LTSPICE_RR0402,ESP32_WROVER_EAGLE-LTSPICE_R0402,R9,"RESISTOR, European symbol",,,,,,,,,,,,,,,,,,,,,,,,,,,,,,,NONE,R,,,,
3,4.7uF,EAGLE-LTSPICE_CC0402,EAGLE-LTSPICE_C0402,"C6, C9, C10","CAPACITOR, European symbol",,,,,,,,,,,,,,,,,,,,,,,,,,,,,,,NONE,C,,,,
2,4.7uF,ESP32_WROVER_EAGLE-LTSPICE_C,ESP32_WROVER_EAGLE-LTSPICE_C0402,"C3, C4","CAPACITOR, European symbol",,,,,,,,,,,,,,,,,,,,,,,,,,,,,,,,,,,,
1,4.7uF/25V,EAGLE-LTSPICE_CC0402,EAGLE-LTSPICE_C0402,C8,"CAPACITOR, European symbol",,,,,,,,,,,,,,,,,,,,,,,,,,,,,,,NONE,C,,,,
1,4.7uF/25V,MBR0530,SOD3716X135N,D3,"ON SEMICONDUCTOR - MBR0530 - DIODE, SCHOTTKY, 0.5A, 30V, SOD-123",,,"In Stock",,https://www.snapeda.com/parts/MBR0530/Onsemi/view-part/?ref=eda,,," Diode Schottky 30 V 500mA Surface Mount SOD-123 ",,,,,,,"ON Semiconductor",,,,,,MBR0530,,"SOD-123-2 ON Semiconductor",,,None,,"https://www.snapeda.com/api/url_track_click_mouser/?unipart_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 Semiconductor&part_name=MBR0530&search_term=None",,https://www.snapeda.com/parts/MBR0530/Onsemi/view-part/?ref=snap,,,,,,
2,5k1,ESP32_WROVER_EAGLE-LTSPICE_RR0402,ESP32_WROVER_EAGLE-LTSPICE_R0402,"R3, R4","RESISTOR, European symbol",,,,,,,,,,,,,,,,,,,,,,,,,,,,,,,NONE,R,,,,
1,68uH,744043680IND_4828-WE-TPC_WRE,IND_4828-WE-TPC_WRE,L1,,,,,,,"Copyright (C) 2024 Ultra Librarian. All rights reserved.",,,,,,,,744043680,,"Wurth Electronics",,,,,,,,,,,,,,,,,,,,
1,BD5229G-TR,BD5229G-TR,SOT95P280X125-5N,IC2,"Voltage Detector with Adjustable Delay Time: CMOS processes are utilized to develop high precision, low current consumption CMOS reset ICs that allow arbitrary setting of the delay time. The extensive lineup includes both Nch Open Drain and CMOS output types in a wide range of detection voltages (from 2.3V to 6.0V, in 0.1V steps), enabling selection of the ideal solution based on customer requirements. In addition, the entire series is of course both lead-free and RoHS-compliant.",,,,,,,,"Voltage Detector with Adjustable Delay Time: CMOS processes are utilized to develop high precision"," low current consumption CMOS reset ICs that allow arbitrary setting of the delay time. The extensive lineup includes both Nch Open Drain and CMOS output types in a wide range of detection voltages (from 2.3V to 6.0V"," in 0.1V steps)"," enabling selection of the ideal solution based on customer requirements. In addition"," the entire series is of course both lead-free and RoHS-compliant.",,,1.25mm,,"ROHM Semiconductor",BD5229G-TR,,,755-BD5229G-TR,https://www.mouser.co.uk/ProductDetail/ROHM-Semiconductor/BD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,,,,,,,,,,,,,,
3,BUTTON_CUSYOMV1,BUTTON_CUSYOMV1,MYBUTTON,"BOOT_BUTTON, CHANGE_BUTTON, RESET_BUTTON",,,,,,,,,,,,,,,,,,,,,,,,,,,,,,,,,,,,,
1,CPH3225A,CPH3225A,CAPCP3225X100N,C28,"Cap 0.011F 3.3V 1210 Flat Check availability",,,"Not in stock",,https://www.snapeda.com/parts/CPH3225A/Seiko+Instruments/vie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,,," 11 mF (EDLC) Supercapacitor 3.3 V 1210 (3225 Metric) - - ",,,,,,,"Seiko Instruments",,,,,,CPH3225A,,"1210 Seiko",,,None,,"https://www.snapeda.com/api/url_track_click_mouser/?unipart_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 Instruments&part_name=CPH3225A&search_term=None",,https://www.snapeda.com/parts/CPH3225A/Seiko+Instruments/vie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,,,,,,
1,DS3231SN#,DS3231SN#,SOIC127P1032X265-16N,U5,"Real Time Clock Serial 16-Pin SOIC W T/R     Check availability",,,"In Stock",,https://www.snapeda.com/parts/DS3231SN%23/Analog+Devices/vie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,,," Extremely Accurate I²C-Integrated RTC/TCXO/Crystal ",,,,,,,"Analog Devices",,,,,,DS3231SN#,,"SOIC-16 Maxim",,,None,,"https://www.snapeda.com/api/url_track_click_mouser/?unipart_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 Devices&part_name=DS3231SN#&search_term=None",,https://www.snapeda.com/parts/DS3231SN%23/Analog+Devices/vie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,,,,,,
1,ESP32-C6-WROOM-1-N8,ESP32-C6-WROOM-1-N8,XCVR_ESP32-C6-WROOM-1-N8,U2,"Check availability",,,"In Stock",,https://www.snapeda.com/parts/ESP32-C6-WROOM-1-N8/Espressif+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,,," Multiprotocol Modules ESP32-C6 module"," Wi-Fi 6 in 2.4 GHz band"," Bluetooth 5"," Zigbee 3.0 and Thread. ESP34-WROOM Compatible - ENGINEERING SAMPLE ",,,,,,,"Espressif Systems",,,,,,ESP32-C6-WROOM-1-N8,,None,,,None,,,,https://www.snapeda.com/parts/ESP32-C6-WROOM-1-N8/Espressif+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,,,
1,ESP32C6_VARISTORCN1812,ESP32C6_VARISTORCN1812,ESP32C6_VARISTOR_CT/CN1812,R2,VARISTOR,,,,,,,,,,,,,,,,,,,,,,,,0,,,,,,,,,,,,
2,ESP32_WROVER_AVX---SD0805S020S1R0_AVX_SD0805S020S1R0_0_0AVX_SD0805S020S1R0_0_0,ESP32_WROVER_AVX---SD0805S020S1R0_AVX_SD0805S020S1R0_0_0AVX_SD0805S020S1R0_0_0,ESP32_WROVER_AVX---SD0805S020S1R0_AVX_SD0805S020S1R0_0,"D1, D6","Schottky Barrier Rectifier Diode",,,,No,,,http://datasheets.avx.com/schottky.pdf,,"DIODE SCHOTTKY 20V 1A 0805",478-7800-1-ND,,yes,,,AVX,,581-SD0805S020S1R0,,,,,,"0805 (2012 metric)",,D,,,,yes,,,,+125°C,-55°C,,
1,ESP32_WROVER_BME680_BME680,ESP32_WROVER_BME680_BME680,ESP32_WROVER_BME680_PSON80P300X300X100-8N,U3,"Integrated Environmental Unit",,,Unavailable,,,,," Integrated Environmental Unit ",,,,,,,"Bosch Sensortec",,,,,,BME680,,"LGA-8 Bosch Tools",,,None,,,,,,,,,,
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
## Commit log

2025-04-06 added files
2025-04-06 added readme
2025-04-06 added license
2025-04-11 added .fbrd board file because in .brd file via stitching disappeared
2025-04-13 fixed review issues
2025-04-16 last minute fix

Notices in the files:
parts and their libraries:
DeskAssistant v19 v1: COPYRIGHT: Copyright (C) 2024 Ultra Librarian. All rights reserved.
